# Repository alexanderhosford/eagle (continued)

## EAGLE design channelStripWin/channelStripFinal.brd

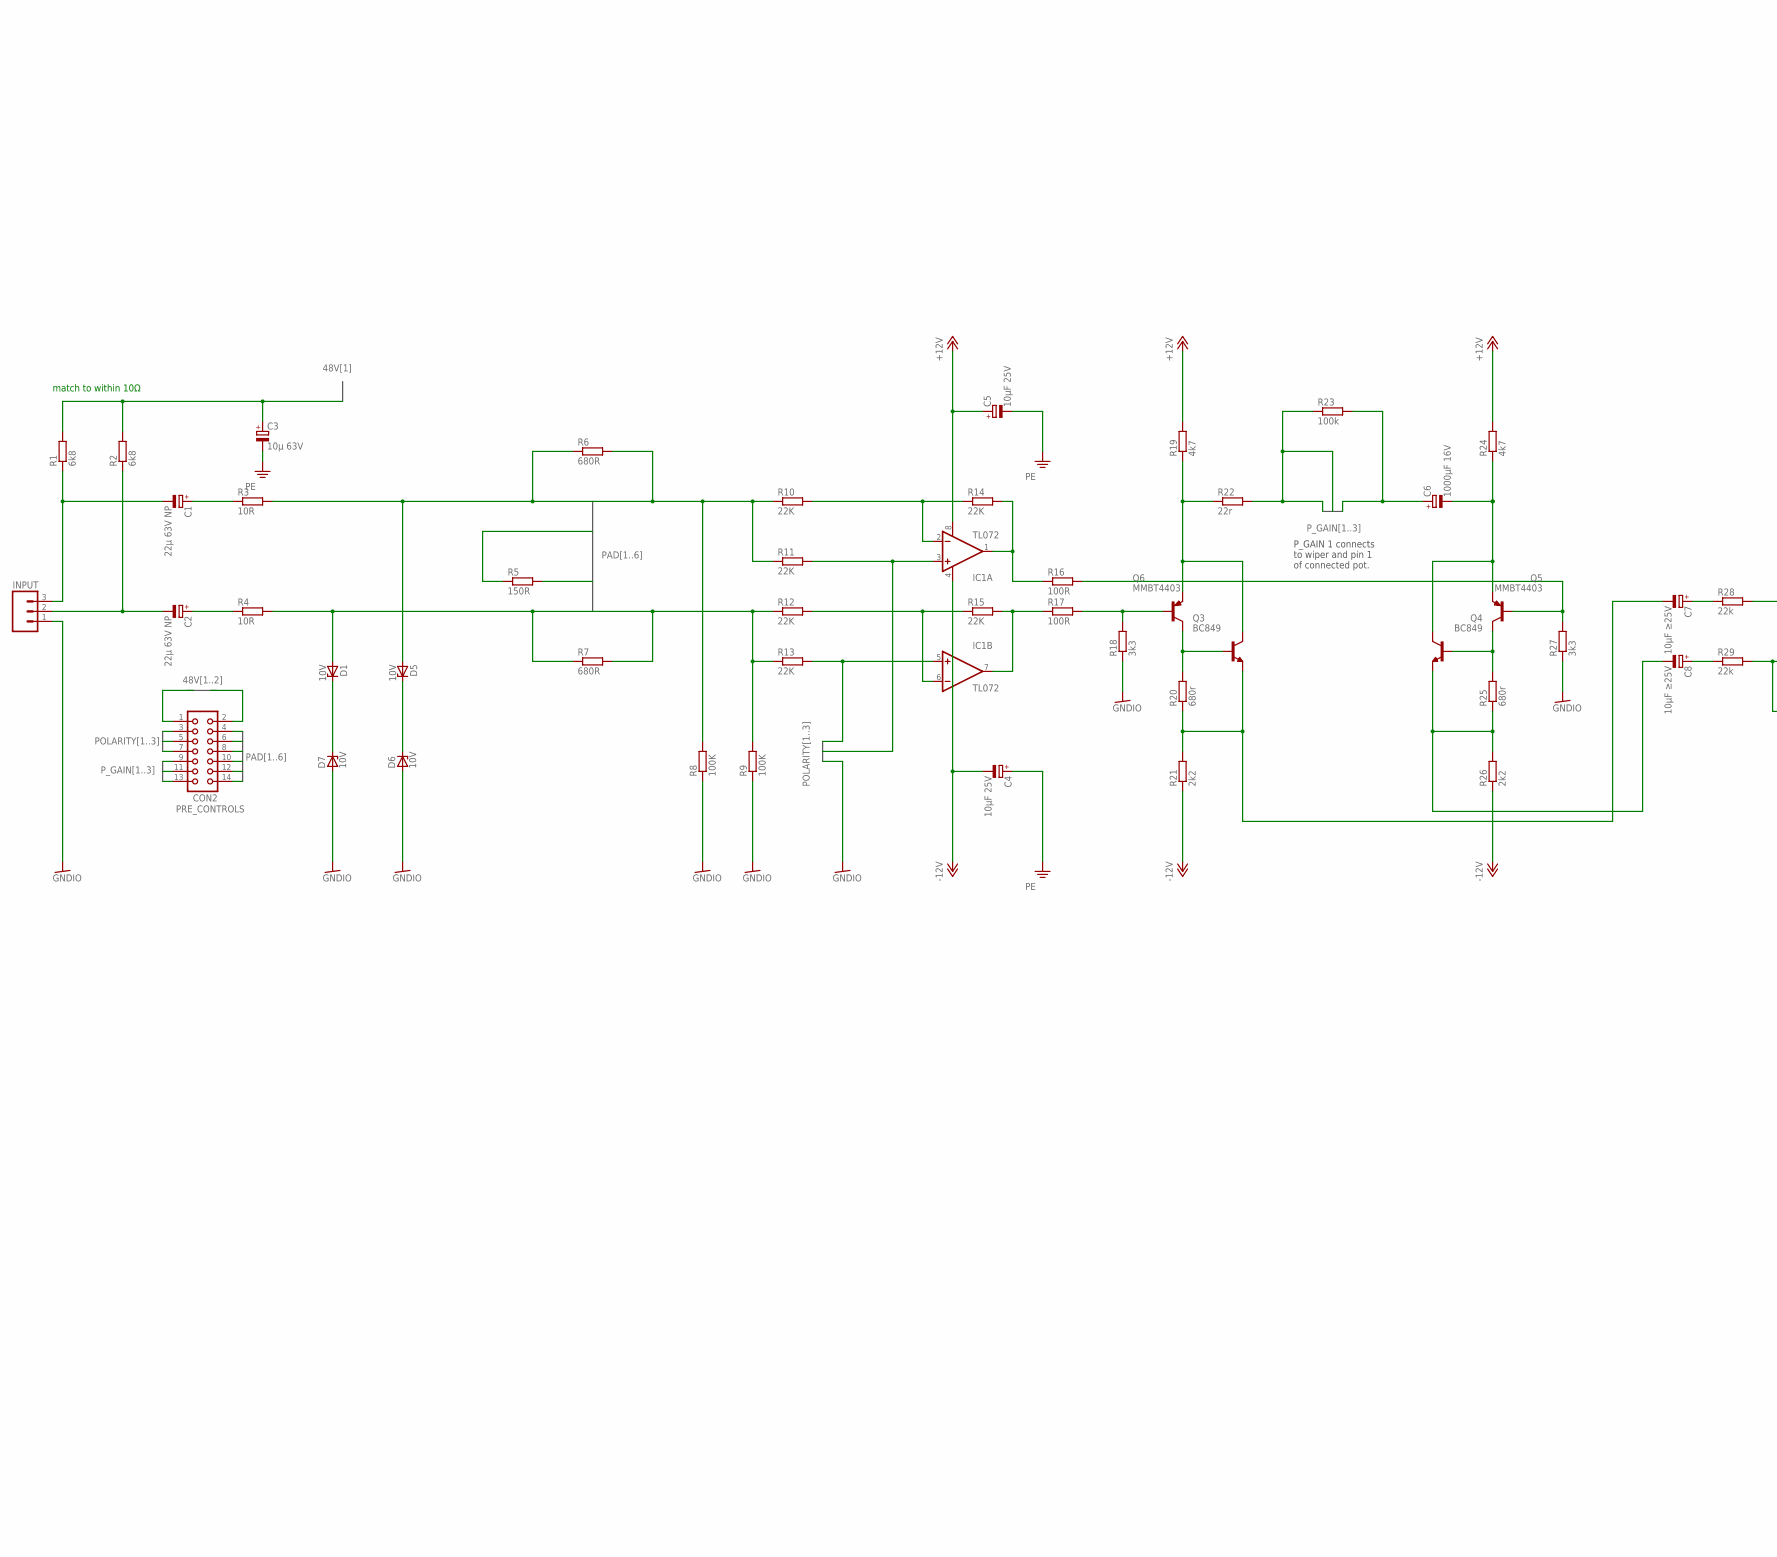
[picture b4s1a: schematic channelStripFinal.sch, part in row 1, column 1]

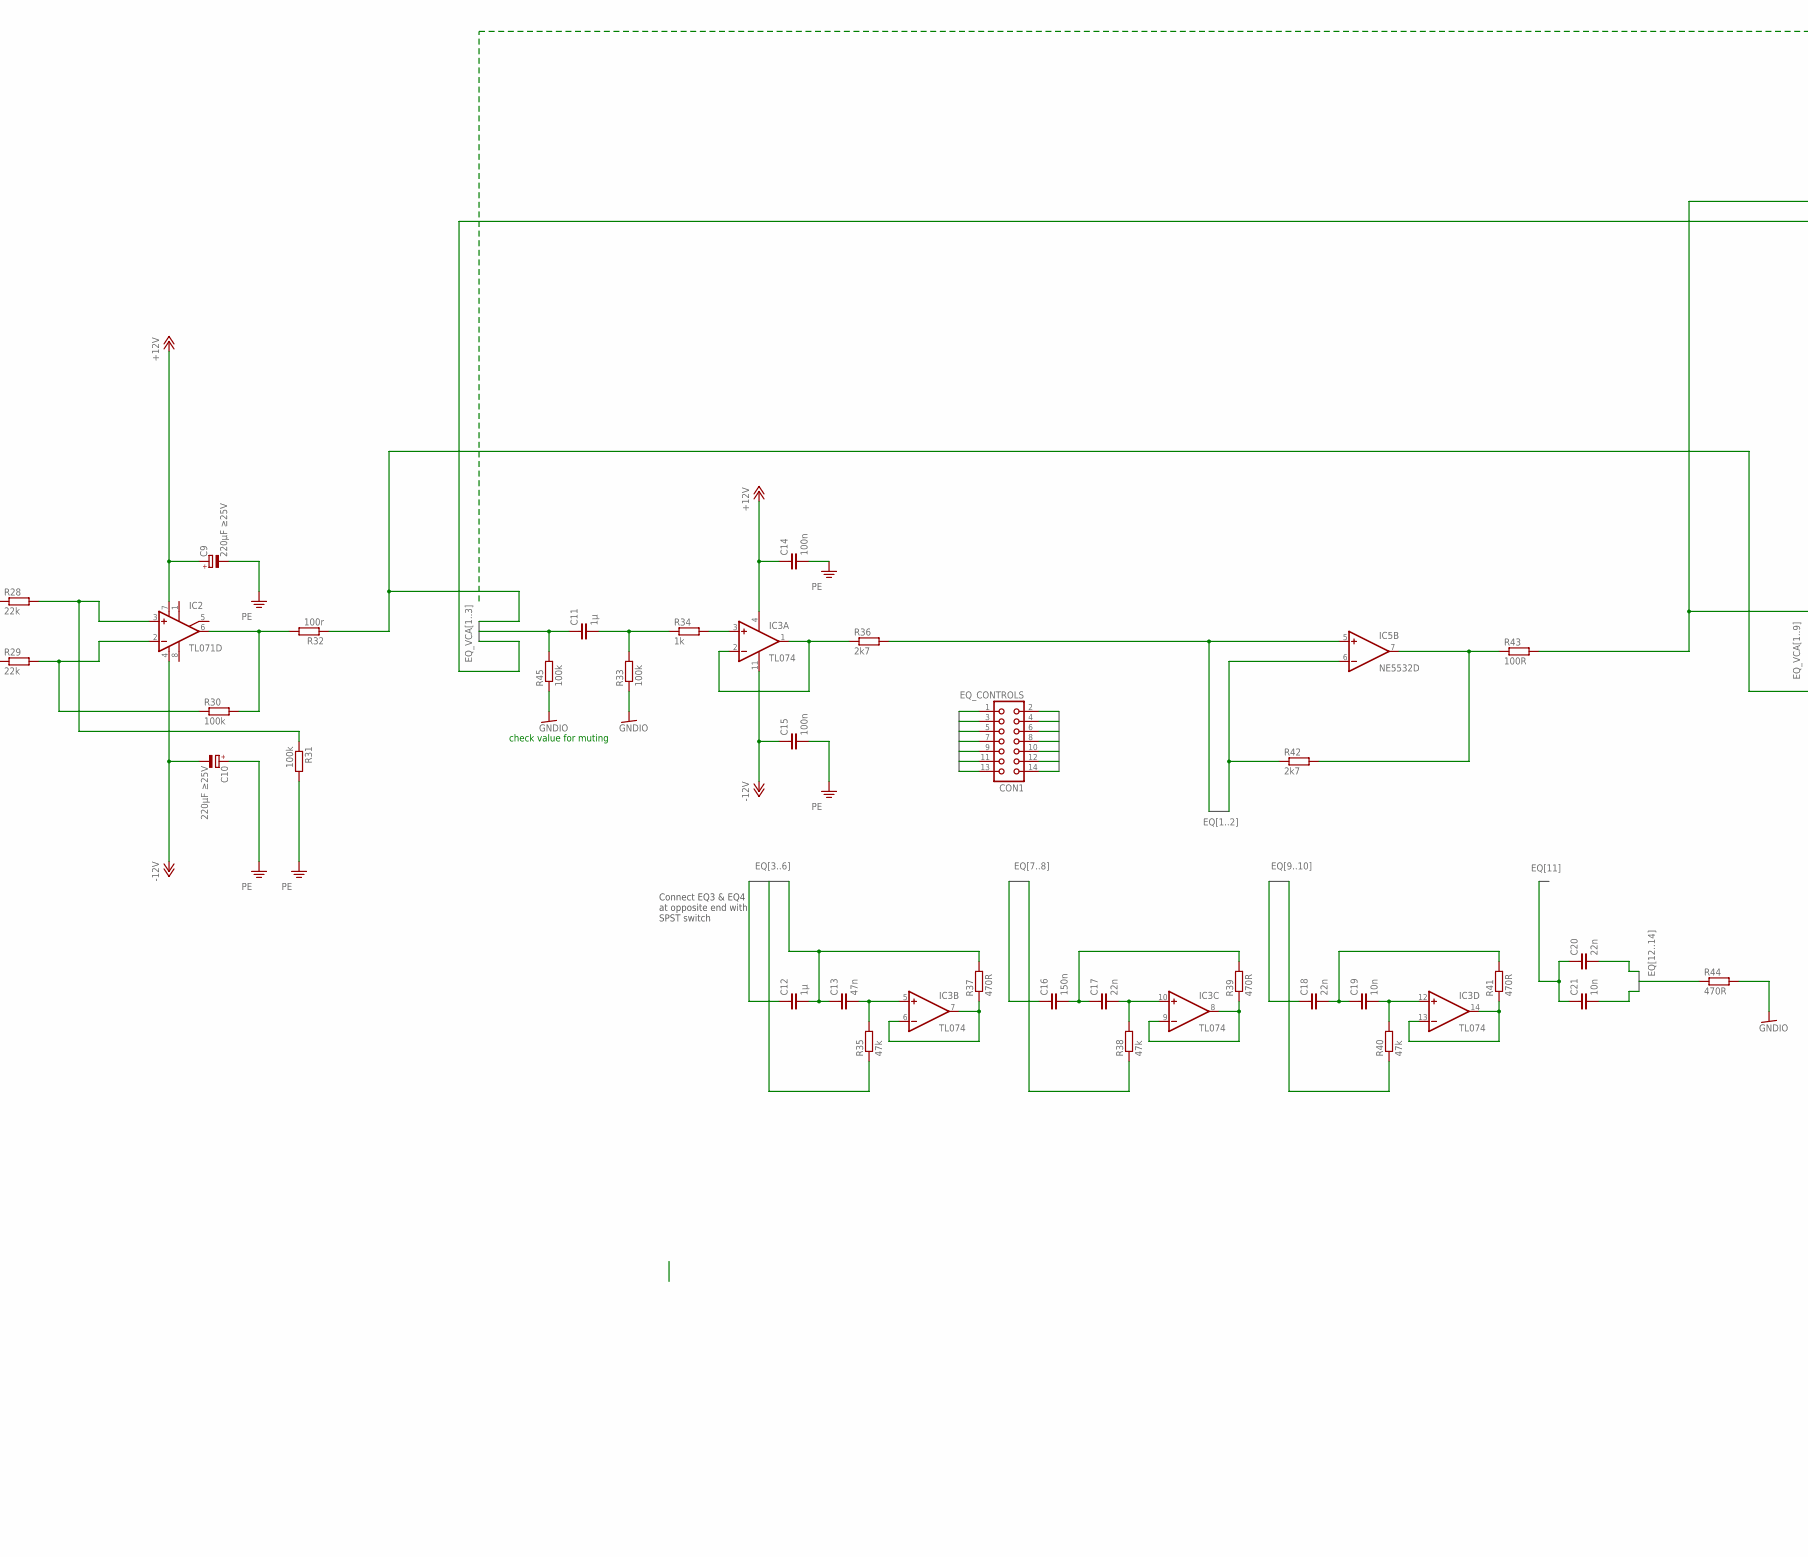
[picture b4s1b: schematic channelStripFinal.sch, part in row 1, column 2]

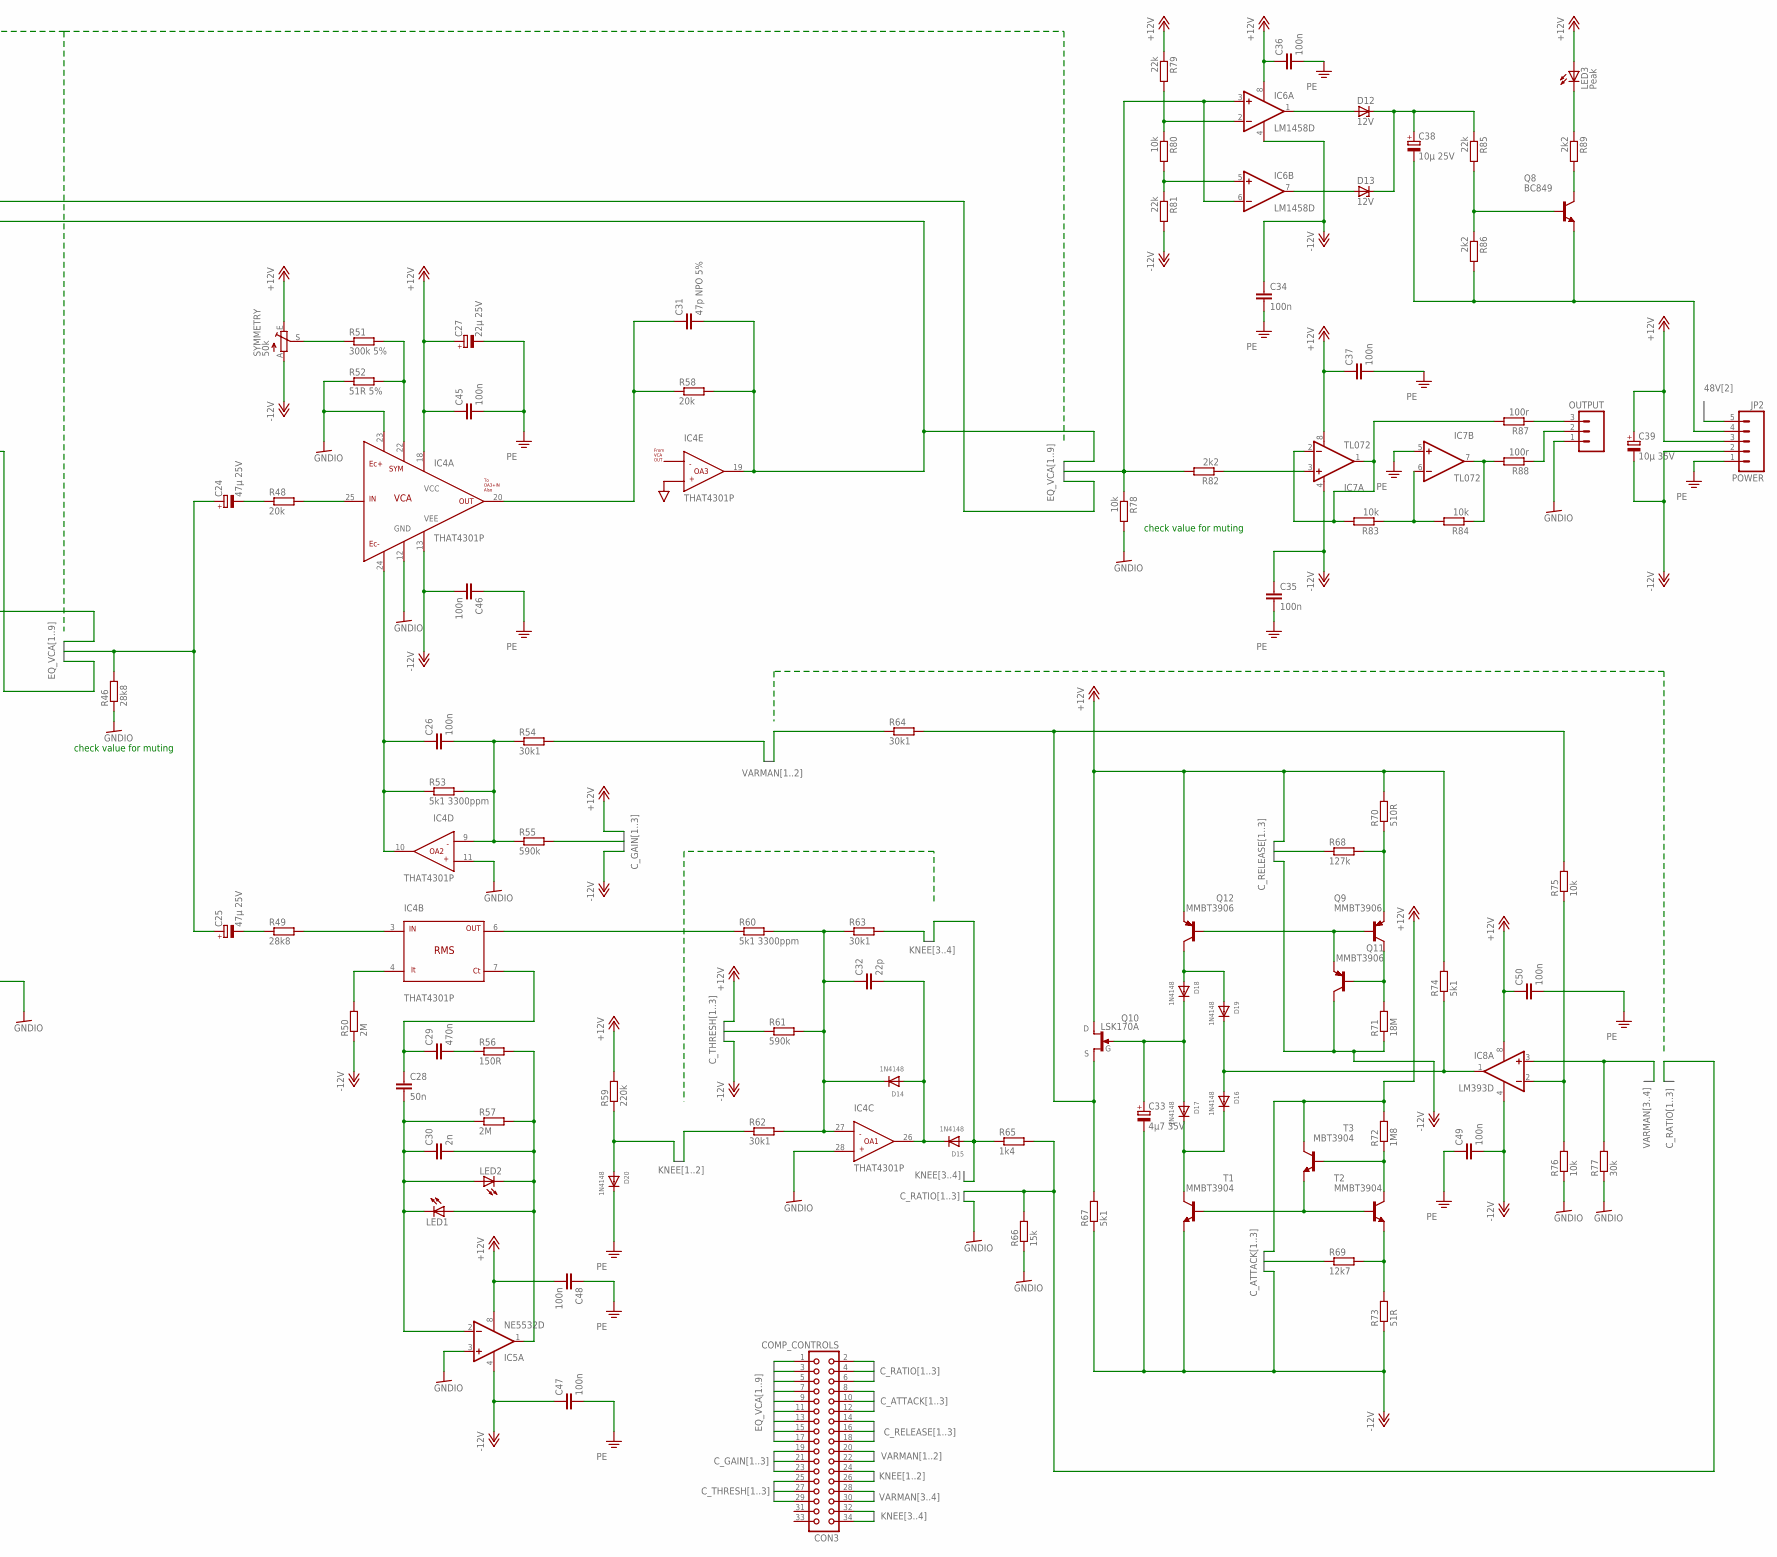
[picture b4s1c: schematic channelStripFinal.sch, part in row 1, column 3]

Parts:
C1, C2: 22µ 63V NP; E5-10,5
C3: 10µ 63V; E2-5
C4, C5: 10µF 25V; E1,8-4
C6: 1000µF 16V; E5-10,5
C7, C8: 10µF ≥25V; E1,8-4
C9, C10: 220µF ≥25V; E3,5-8
C11, C12: 1µ; C050-050X075
C13: 47n; C050-025X075
C14, C15, C26, C34, C35, C36, C37, C45, C46, C47, C48, C49, C50: 100n; C050-025X075
C16: 150n; C075-032X103
C17, C18, C20: 22n; C075-032X075
C19, C21: 10n; C050-025X075
C24, C25: 47µ 25V; E2,5-6
C27: 22µ 25V; E2-5
C28: 50n; C050-025X075
C29: 470n; C050-035X075
C30: 2n; C025-024X044
C31: 47p NPO 5%; C025-024X044
C32: 22p; C025-024X044
C33: 4µ7 35V; E2-4
C38: 10µ 25V; E1,8-4
C39: 10µ 35V; E1,8-4
CON1: EQ_CONTROLS; CON14
CON2: PRE_CONTROLS; CON14
CON3: COMP_CONTROLS; CON34
D1, D5, D6, D7: 10V; ZD-5-SMALLSILK
D12, D13: 12V; ZD-5-SMALLSILK
D14, D15, D16, D17, D18, D19, D20: 1N4148; SOD-123
IC1, IC7: TL072; SO08
IC2: TL071D; SO08
IC3: TL074; SO14
IC4: THAT4301P; SO30W
IC5: NE5532D; SO08
IC6: LM1458D; SO08
IC8: LM393D; SO08
INPUT: M03PTH; 1X03
JP2: POWER; 1X05
LED1, LED2: LED1206; LED-1206
LED3: Peak; LED-1206
OUTPUT: M03PTH; 1X03
Q3, Q4, Q8: BC849; SOT23
Q5, Q6: MMBT4403; SOT23-BEC
Q9, Q11, Q12: MMBT3906; SOT23-BEC
Q10: LSK170A; SOT23
R1, R2: 6k8; R1206
R3, R4: 10R; R1206
R5, R56: 150R; R1206
R6, R7: 680R; R1206
R8, R9: 100K; R1206
R10, R11, R12, R13, R14, R15: 22K; R1206
R16, R17, R43: 100R; R1206
R18, R27: 3k3; R1206
R19, R24: 4k7; R1206
R20, R25: 680r; R1206
R21, R26, R82, R86, R89: 2k2; R1206
R22: 22r; R1206
R23, R30, R31, R33, R45: 100k; R1206
R28, R29, R79, R81, R85: 22k; R1206
R32, R87, R88: 100r; R1206
R34: 1k; R1206
R35, R38, R40: 47k; R1206
R36, R42: 2k7; R1206
R37, R39, R41, R44: 470R; R1206
R46, R49: 28k8; R1206
R48, R58: 20k; R1206
R50, R57: 2M; R1206
R51: 300k 5%; R1206
R52: 51R 5%; R1206
R53, R60: 5k1 3300ppm; R1206
R54, R62, R63, R64: 30k1; R1206
R55, R61: 590k; R1206
R59: 220k; R1206
R65: 1k4; R1206
R66: 15k; R1206
R67, R74: 5k1; R1206
R68: 127k; R1206
R69: 12k7; R1206
R70: 510R; R1206
R71: 18M; R1206
R72: 1M8; R1206
R73: 51R; R1206
R75, R76, R78, R80, R83, R84: 10k; R1206
R77: 30k; R1206
SYMMETRY: 50k; B64W
T1, T2: MMBT3904; SOT23-BEC
T3: MBT3904; SOT23-BEC

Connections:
48V1: CON2.1
48V2: CON2.2, JP2.5
+12V: C5.+, C9.+, C14.1, C27.+, C36.1, C37.1, C39.+, C45.1, C48.2, C50.1, IC1.8 (V+), IC2.7 (V+), IC3.4 (V+), IC4.18 (VCC), IC5.8 (V+), IC6.8 (V+), IC7.8 (V+), IC8.8 (V+), JP2.3, LED3.A, R19.2, R24.2, R59.2, R79.1, SYMMETRY.E
-12V: C4.-, C10.-, C15.1, C34.1, C35.1, C39.-, C46.2, C47.1, C49.2, IC1.4 (V-), IC2.4 (V-), IC3.11 (V-), IC4.13 (VEE), IC5.4 (V-), IC6.4 (V-), IC7.4 (V-), IC8.4 (V-), JP2.2, R21.1, R26.1, R50.1, R81.2, SYMMETRY.A
C_ATTACK1: CON3.8, R72.2, T3.C
C_ATTACK2: CON3.10, R69.1
C_ATTACK3: C33.-, CON3.12, R67.1, R73.1, T1.E
C_GAIN1: CON3.19
C_GAIN2: CON3.21, R55.2
C_GAIN3: CON3.23
C_RATIO1: CON3.2
C_RATIO2: CON3.4, R65.2, R66.2
C_RATIO3: CON3.6
C_RELEASE1: CON3.14, Q10.1 (D), Q12.E, R70.2, R74.2
C_RELEASE2: CON3.16, R68.1
C_RELEASE3: CON3.18, Q11.C, R71.1
C_THRESH1: CON3.25
C_THRESH2: CON3.27, R61.1
C_THRESH3: CON3.29
EQ1: CON1.1, IC5.5 (+IN), R36.2
EQ2: CON1.2, IC5.6 (-IN), R42.1
EQ3: C12.1, CON1.3
EQ4: C12.2, C13.1, CON1.4, R37.2
EQ5: CON1.5, R35.1
EQ6: CON1.6
EQ7: C16.1, CON1.7
EQ8: CON1.8, R38.1
EQ9: C18.1, CON1.9
EQ10: CON1.10, R40.1
EQ11: C20.1, C21.1, CON1.11
EQ12: C20.2, CON1.12
EQ13: C21.2, CON1.13
EQ14: CON1.14, R44.1
EQ_VCA1: CON3.1, R32.1
EQ_VCA2: C11.1, CON3.3, R45.2
EQ_VCA3: C31.2, CON3.5, IC4.19 (OA3_OUT), R58.2
EQ_VCA4: CON3.7, R43.2
EQ_VCA5: C24.+, C25.+, CON3.9, R46.2
EQ_VCA6: CON3.11
EQ_VCA7: CON3.13
EQ_VCA8: CON3.15, IC6.3 (+IN), IC6.6 (-IN), R78.1, R82.2
EQ_VCA9: CON3.17
GNDIO: D6.A, D7.A, IC4.11 (OA2+IN), IC4.12 (GND), IC4.23 (EC+), IC4.28 (OA1+IN), IC5.3 (+IN), INPUT.1, OUTPUT.1, R8.1, R9.1, R18.1, R27.1, R33.1, R44.2, R45.1, R46.1, R52.1, R66.1, R76.1, R77.1, R78.2
KNEE1: CON3.24, D20.A, R59.1
KNEE2: CON3.26, R62.1
KNEE3: CON3.32, R63.2
KNEE4: CON3.34, D15.A, R65.1
unnamed: IC7.7 (OUT), R84.1, R88.2
unnamed: C7.-, Q3.2 (E), R20.1, R21.2
unnamed: C16.2, C17.1, R39.2
unnamed: C18.2, C19.1, R41.2
unnamed: IC3.13 (-IN), IC3.14 (OUT), R41.1
unnamed: C19.2, IC3.12 (+IN), R40.2
unnamed: C11.2, R33.2, R34.1
unnamed: IC3.3 (+IN), R34.2
unnamed: IC3.1 (OUT), IC3.2 (-IN), R36.1
unnamed: IC5.7 (OUT), R42.2, R43.1
unnamed: Q8.1 (B), R85.2, R86.1
unnamed: C1.+, R3.1
unnamed: IC3.6 (-IN), IC3.7 (OUT), R37.1
unnamed: C13.2, IC3.5 (+IN), R35.2
unnamed: IC3.8 (OUT), IC3.9 (-IN), R39.1
unnamed: C2.+, R4.1
unnamed: C17.2, IC3.10 (+IN), R38.2
unnamed: IC6.2 (-IN), R79.2, R80.1
unnamed: C1.-, INPUT.3, R1.1
unnamed: C2.-, INPUT.2, R2.1
unnamed: OUTPUT.2, R88.1
unnamed: OUTPUT.3, R87.1
unnamed: IC2.3 (+IN), R28.2, R31.1
unnamed: IC7.6 (-IN), R83.1, R84.2
unnamed: IC7.1 (OUT), IC7.2 (-IN), R83.2, R87.2
unnamed: IC7.3 (+IN), R82.1
unnamed: C7.+, R28.1
unnamed: IC2.6 (OUT), R30.2, R32.2
unnamed: IC2.2 (-IN), R29.2, R30.1
unnamed: C8.+, R29.1
unnamed: C6.-, Q4.3 (C), Q5.E, R24.1
unnamed: Q3.3 (C), Q6.E, R19.1, R22.1
unnamed: Q4.1 (B), Q5.C, R25.2
unnamed: IC1.1 (OUT), R14.2, R16.1
unnamed: Q3.1 (B), Q6.C, R20.2
unnamed: IC6.5 (+IN), R80.2, R81.1
unnamed: IC1.7 (OUT), R15.2, R17.1
unnamed: C8.-, Q4.2 (E), R25.1, R26.2
unnamed: Q5.B, R16.2, R27.2
unnamed: Q6.B, R17.2, R18.2
unnamed: IC1.6 (-IN), R12.2, R15.1
unnamed: D5.C, D6.C
unnamed: IC1.2 (-IN), R10.2, R14.1
unnamed: D1.C, D7.C
unnamed: Q8.3 (C), R89.2
unnamed: C38.+, D12.C, D13.C, R85.1
unnamed: LED3.C, R89.1
unnamed: D12.A, IC6.1 (OUT)
unnamed: D13.A, IC6.7 (OUT)
unnamed: IC4.25 (VCA_IN), R48.2
unnamed: C24.-, R48.1
unnamed: R51.1, SYMMETRY.S
unnamed: IC4.22 (SYM), R51.2, R52.2
unnamed: C31.1, IC4.20 (VCA_OUT), R58.1
unnamed: C26.1, IC4.10 (OA2_OUT), IC4.24 (EC-), R53.1
unnamed: C26.2, IC4.9 (OA2-IN), R53.2, R54.1, R55.1
unnamed: C29.2, R56.1
unnamed: C28.1, C29.1, IC4.7 (CT)
unnamed: C28.2, C30.1, IC5.2 (-IN), LED1.C, LED2.A, R57.1
unnamed: C30.2, IC5.1 (OUT), LED1.A, LED2.C, R56.2, R57.2
unnamed: IC4.4 (IT), R50.2
unnamed: IC4.3 (RMS_IN), R49.2
unnamed: C25.-, R49.1
unnamed: IC4.6 (RMS_OUT), R60.1
unnamed: C32.1, D14.C, IC4.27 (OA1-IN), R60.2, R61.2, R62.2, R63.1
unnamed: C32.2, D14.A, D15.C, IC4.26 (OA1_OUT)
unnamed: Q10.2 (S), R64.2, R67.2, R75.2
unnamed: C33.+, D17.A, D18.C, Q10.3 (G)
unnamed: D16.C, D17.C, T1.C
unnamed: D18.A, D19.A, Q12.C
unnamed: D16.A, D19.C, IC8.1 (OUT), R74.1
unnamed: T1.B, T2.B, T3.E
unnamed: R69.2, R73.2, T2.E
unnamed: R72.1, T2.C, T3.B
unnamed: Q9.B, Q11.E, Q12.B
unnamed: Q9.C, Q11.B, R71.2
unnamed: Q9.E, R68.2, R70.1
unnamed: IC8.2 (-IN), R75.1, R76.2
PAD1: CON2.4, R5.1
PAD2: CON2.6, R6.2, R8.2, R10.1, R11.1
PAD3: CON2.8, D5.A, R3.2, R6.1
PAD4: CON2.10, R5.2
PAD5: CON2.12, R7.2, R9.2, R12.1, R13.1
PAD6: CON2.14, D1.A, R4.2, R7.1
PE: C3.-, C4.+, C5.-, C9.-, C10.+, C14.2, C15.2, C27.-, C34.2, C35.2, C36.2, C37.2, C45.2, C46.1, C47.2, C48.1, C49.1, C50.2, D20.C, IC7.5 (+IN), JP2.1, R31.2
PEAKGND: C38.-, JP2.4, Q8.2 (E), R86.2
POLARITY1: CON2.3, IC1.5 (+IN), R13.2
POLARITY2: CON2.5, IC1.3 (+IN), R11.2
POLARITY3: CON2.7
PRE1: C3.+, R1.2, R2.2
P_GAIN1: CON2.9, R22.2, R23.1
P_GAIN2: CON2.11
P_GAIN3: C6.+, CON2.13, R23.2
VARMAN1: CON3.20, R54.2
VARMAN2: CON3.22, R64.1
VARMAN3: CON3.28, IC8.3 (+IN), R77.2
VARMAN4: CON3.30

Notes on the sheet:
match to within 10Ω
check value for muting
Connect EQ3 & EQ4 at opposite end with SPST switch
P_GAIN 1 connects to wiper and pin 1 of connected pot.

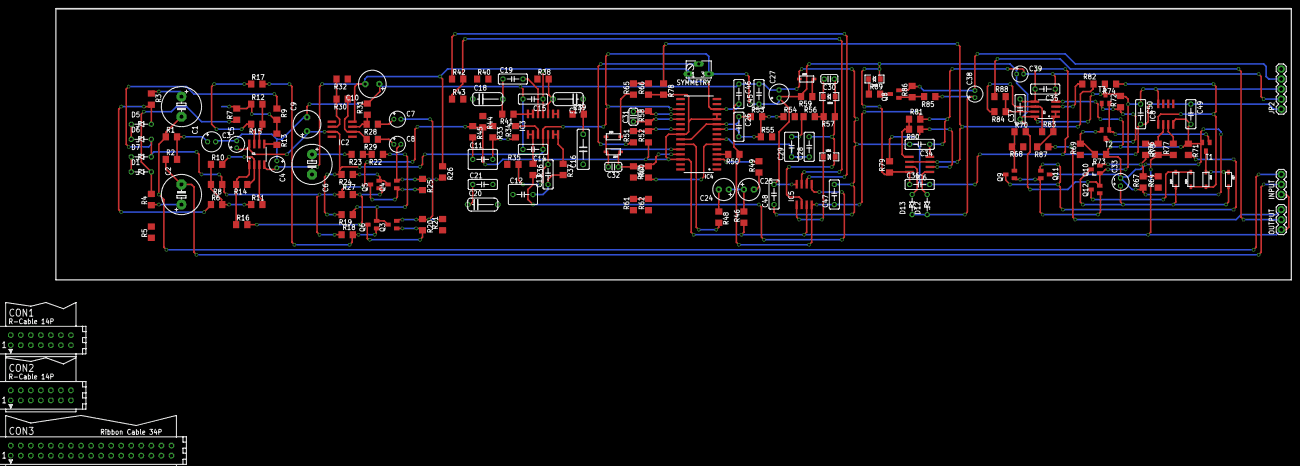
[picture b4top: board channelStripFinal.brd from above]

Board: 2 copper layers, 312.4 x 68.6 mm, 174 parts (0 on the bottom side), 130 nets.

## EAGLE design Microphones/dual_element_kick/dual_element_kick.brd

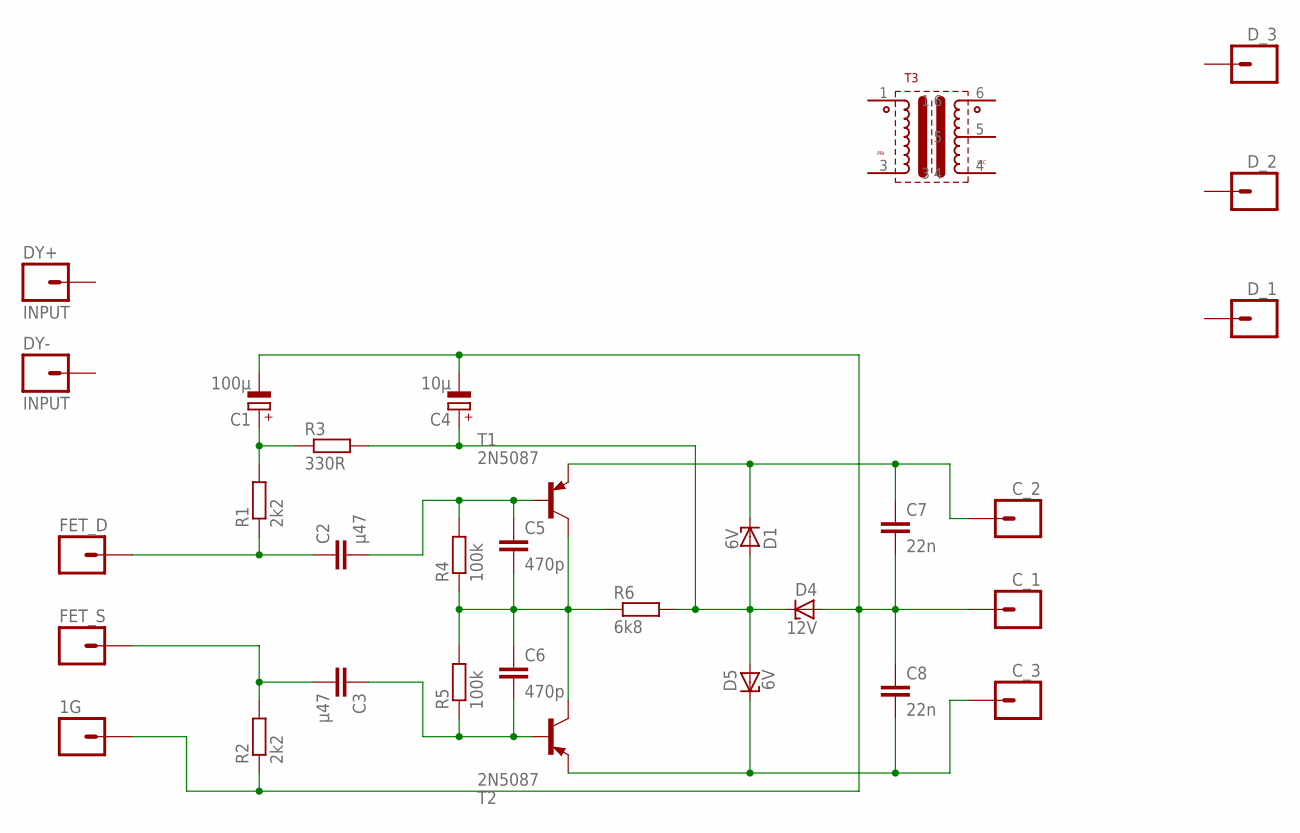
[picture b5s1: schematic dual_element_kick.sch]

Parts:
1G: M01PTH; 1X01
C1: 100µ; E3,5-8
C2, C3: µ47; C050-045X075
C4: 10µ; E2-4
C5, C6: 470p; C025-024X044
C7, C8: 22n; C025-024X044
C_1, C_2, C_3: M01PTH; 1X01
D1, D5: 6V; ZD-5-SMALLSILK
D4: 12V; ZD-5-SMALLSILK
DY+: INPUT; 1X01
DY-: INPUT; 1X01
D_1, D_2, D_3: M01PTH; 1X01
FET_D: M01PTH; 1X01
FET_S: M01PTH; 1X01
R1, R2: 2k2; 0207/2V
R3: 330R; 0207/2V
R4, R5: 100k; 0207/2V
R6: 6k8; 0207/2V
T1, T2: 2N5087; TO92-EBC
T3: OEP-Z1604

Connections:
5: T3.5
GND: 1G.1, C1.-, C4.-, C7.2, C8.1, C_1.1, D4.A, R2.1
unnamed: C4.+, D1.A, D4.C, D5.A, R3.2, R6.2
unnamed: C5.2, C6.1, R4.1, R5.2, R6.1, T1.C, T2.C
unnamed: C7.1, C_2.1, D1.C, T1.E
unnamed: C8.2, C_3.1, D5.C, T2.E
unnamed: C2.2, C5.1, R4.2, T1.B
unnamed: C3.1, C6.2, R5.1, T2.B
unnamed: C1.+, R1.2, R3.1
unnamed: C2.1, FET_D.1, R1.1
unnamed: C3.2, FET_S.1, R2.2

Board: 2 copper layers, 31 parts (0 on the bottom side), 10 nets, no tracks yet.

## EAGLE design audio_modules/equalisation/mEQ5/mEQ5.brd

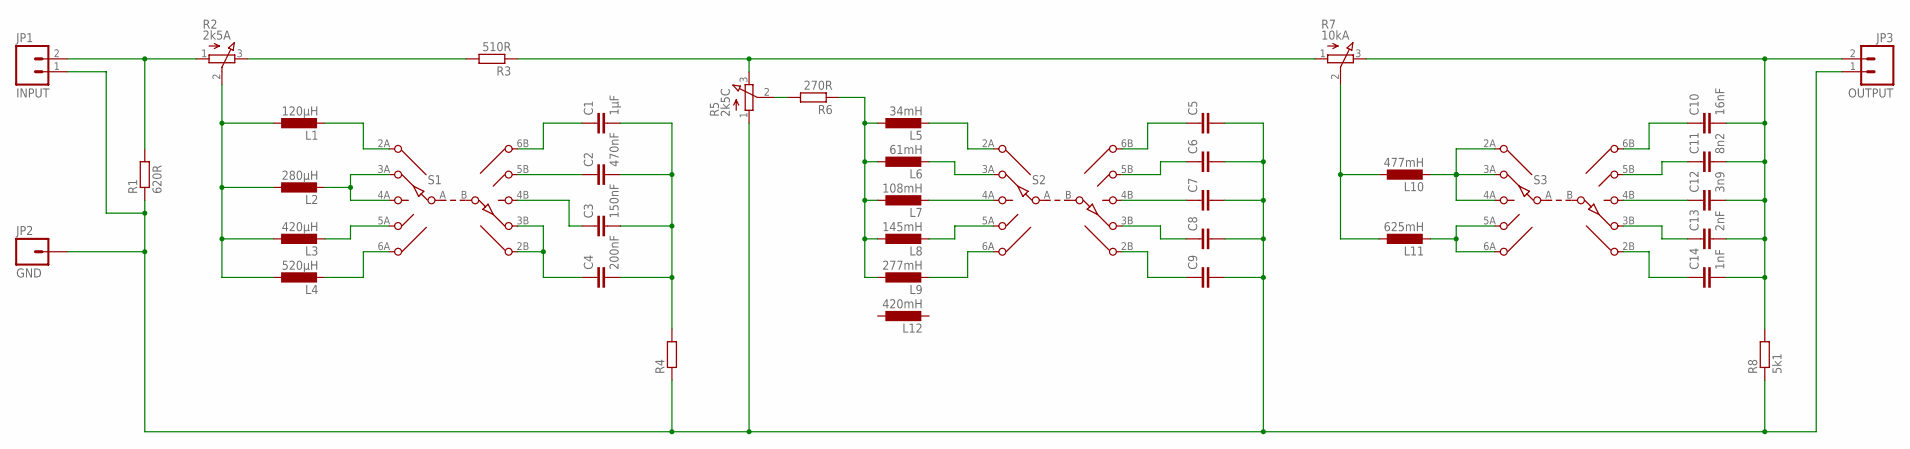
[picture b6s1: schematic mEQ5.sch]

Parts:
C1: 1µF; C050-025X075
C2: 470nF; C050-025X075
C3: 150nF; C050-025X075
C4: 200nF; C050-025X075
C5, C6, C7, C8, C9: C-EU050-025X075; C050-025X075
C10: 16nF; C050-025X075
C11: 8n2; C050-025X075
C12: 3n9; C050-025X075
C13: 2nF; C050-025X075
C14: 1nF; C050-025X075
JP1: INPUT; SCREWTERMINAL-3.5MM-2
JP2: GND; 1X01_LONGPAD
JP3: OUTPUT; SCREWTERMINAL-3.5MM-2
L1: 120µH; 0207/10
L2: 280µH; 0207/10
L3: 420µH; 0207/10
L4: 520µH; 0207/10
L5: 34mH; 0207/10
L6: 61mH; 0207/10
L7: 108mH; 0207/10
L8: 145mH; 0207/10
L9: 277mH; 0207/10
L10: 477mH; 0207/10
L11: 625mH; 0207/10
L12: 420mH; 0207/10
R1: 620R; 0207/10
R2: 2k5A; 3RP/1610N
R3: 510R; 0207/10
R4: R-EU_0207/10; 0207/10
R5: 2k5C; 3RP/1610N
R6: 270R; 0207/10
R7: 10kA; 3RP/1610N
R8: 5k1; 0207/10
S1, S2, S3: 5-POS-DP-ROTARY-SWITCH; 5-POS-DP-ROTARY

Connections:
unnamed: C3.1, S1.4B (2)
unnamed: L10.2, S3.2A (7), S3.3A (3), S3.4A (5)
unnamed: L1.2, S1.2A (7)
unnamed: L2.2, S1.3A (3), S1.4A (5)
unnamed: L11.2, S3.5A (6), S3.6A (9)
unnamed: C10.1, S3.6B (10)
unnamed: L3.2, S1.5A (6)
unnamed: L4.2, S1.6A (9)
unnamed: C1.1, S1.6B (10)
unnamed: C2.1, S1.5B (4)
unnamed: C4.1, S1.2B (8), S1.3B (1)
unnamed: C11.1, S3.5B (4)
unnamed: C12.1, S3.4B (2)
unnamed: C13.1, S3.3B (1)
unnamed: C14.1, S3.2B (8)
unnamed: L5.2, S2.2A (7)
unnamed: L6.2, S2.3A (3)
unnamed: L7.2, S2.4A (5)
unnamed: L8.2, S2.5A (6)
unnamed: L9.2, S2.6A (9)
unnamed: C5.1, S2.6B (10)
unnamed: C6.1, S2.5B (4)
unnamed: C7.1, S2.4B (2)
unnamed: C8.1, S2.3B (1)
unnamed: C9.1, S2.2B (8)
unnamed: L1.1, L2.1, L3.1, L4.1, R2.2 (S)
unnamed: JP1.2, R1.2, R2.1 (A)
unnamed: C1.2, C2.2, C3.2, C4.2, R4.2
unnamed: R2.3 (E), R3.2
unnamed: R3.1, R5.3 (E), R7.1 (A)
unnamed: R5.2 (S), R6.2
unnamed: L5.1, L6.1, L7.1, L8.1, L9.1, R6.1
unnamed: L10.1, L11.1, R7.2 (S)
unnamed: C5.2, C6.2, C7.2, C8.2, C9.2, JP1.1, JP2.1, JP3.1, R1.1, R4.1, R5.1 (A), R8.1
unnamed: C10.2, C11.2, C12.2, C13.2, C14.2, JP3.2, R7.3 (E), R8.2

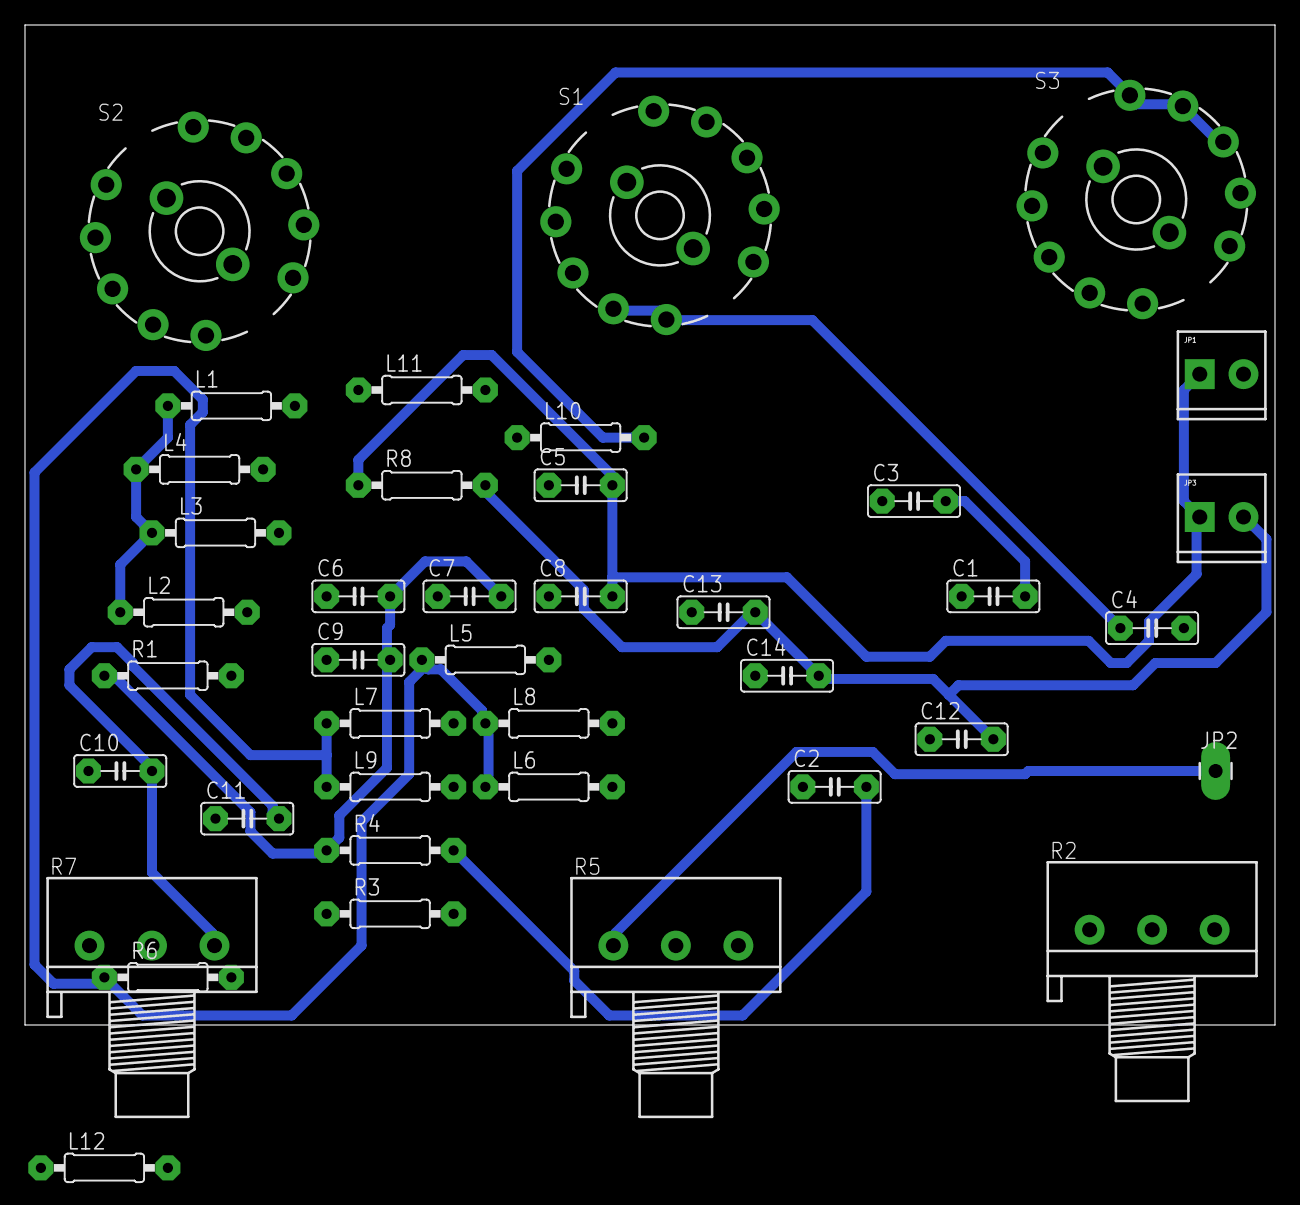
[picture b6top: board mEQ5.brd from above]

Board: 2 copper layers, 100.0 x 80.0 mm, 40 parts (0 on the bottom side), 35 nets.

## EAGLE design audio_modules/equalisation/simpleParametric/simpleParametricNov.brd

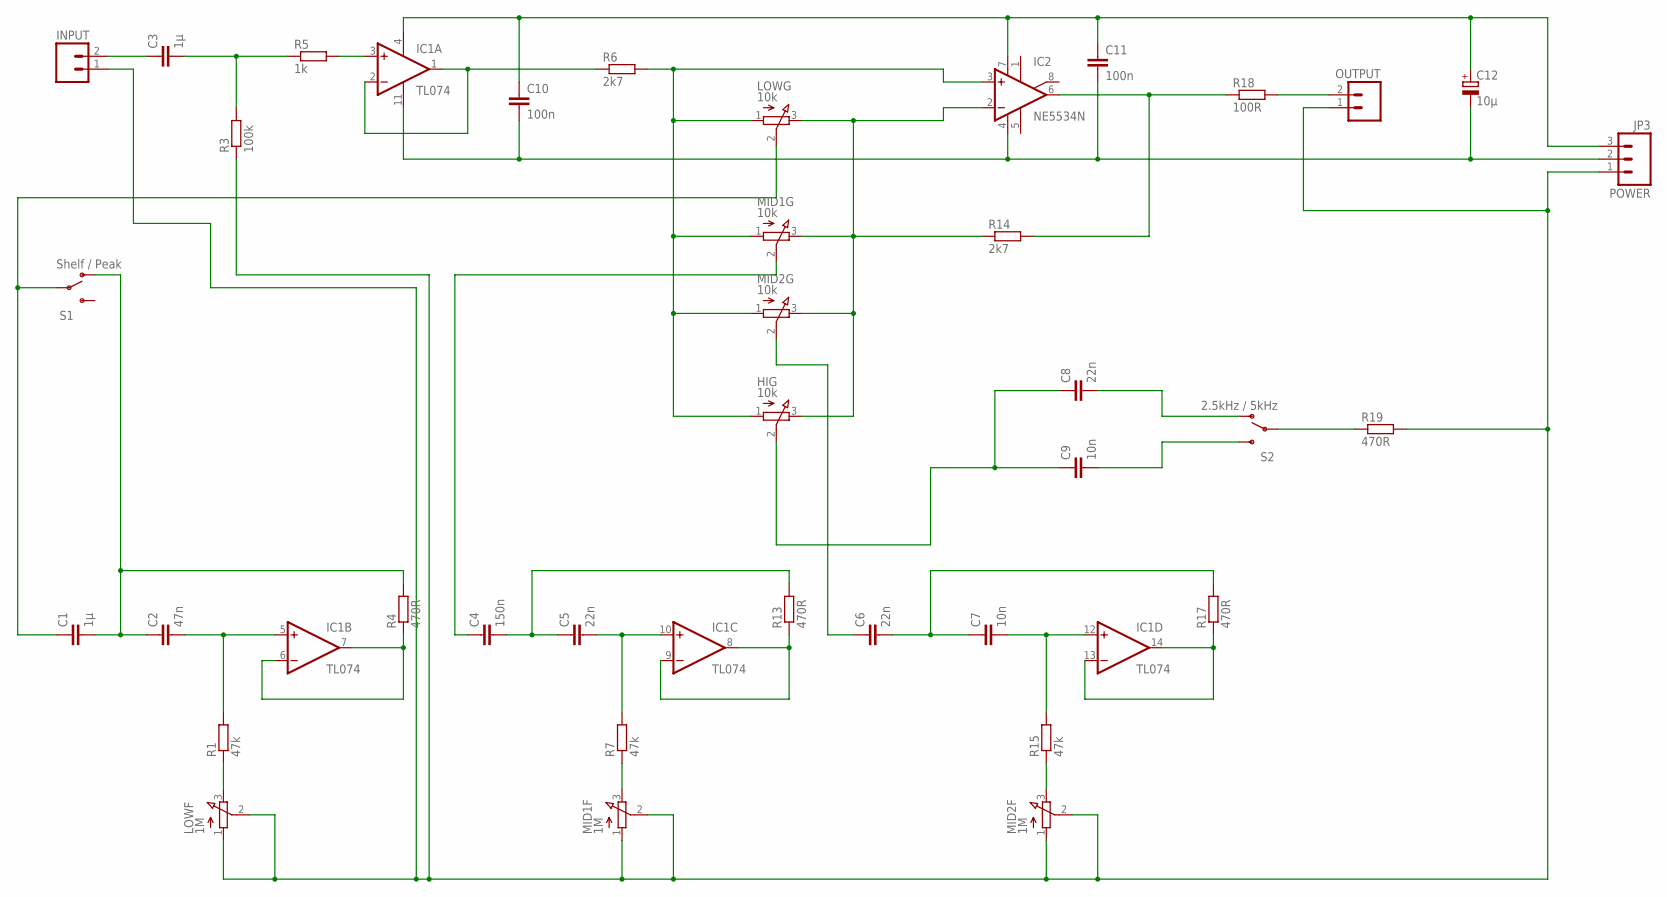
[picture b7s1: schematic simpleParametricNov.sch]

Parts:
C1, C3: 1µ; C050-025X075
C2: 47n; C050-025X075
C4: 150n; C050-025X075
C5, C6, C8: 22n; C025-024X044
C7, C9: 10n; C025-024X044
C10, C11: 100n; C050-025X075
C12: 10µ; E2,5-6E
HIG: 10k; 3RP/1610N
IC1: TL074; DIL14
IC2: NE5534N; DIL08
INPUT: M02PTH; 1X02
JP3: POWER; SCREWTERMINAL-3.5MM-3
LOWF: 1M; 3RP/1610N
LOWG: 10k; 3RP/1610N
MID1F, MID2F: 1M; 3RP/1610N
MID1G, MID2G: 10k; 3RP/1610N
OUTPUT: M02PTH; 1X02
R1, R7, R15: 47k; 0207/7
R3: 100k; 0207/7
R4, R13, R17, R19: 470R; 0207/7
R5: 1k; 0207/7
R6, R14: 2k7; 0207/7
R18: 100R; 0207/7
S1: Shelf / Peak; SWITCH-SPDT
S2: 2.5kHz / 5kHz; SWITCH-SPDT

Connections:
GND: INPUT.1, JP3.1, LOWF.1 (A), LOWF.2 (S), MID1F.1 (A), MID1F.2 (S), MID2F.1 (A), MID2F.2 (S), OUTPUT.1, R3.1, R19.2
unnamed: C1.2, C2.1, R4.2, S1.1 (O)
unnamed: C4.2, C5.1, R13.2
unnamed: C6.2, C7.1, R17.2
unnamed: C9.2, S2.3 (S)
unnamed: C8.2, S2.1 (O)
unnamed: R19.1, S2.2
unnamed: IC1.13 (-IN), IC1.14 (OUT), R17.1
unnamed: C7.2, IC1.12 (+IN), R15.2
unnamed: MID2F.3 (E), R15.1
unnamed: C3.1, INPUT.2
unnamed: C3.2, R3.2, R5.1
unnamed: IC1.3 (+IN), R5.2
unnamed: IC1.1 (OUT), IC1.2 (-IN), R6.1
unnamed: HIG.1 (A), IC2.3 (+IN), LOWG.1 (A), MID1G.1 (A), MID2G.1 (A), R6.2
unnamed: IC2.6 (OUT), R14.2, R18.1
unnamed: OUTPUT.2, R18.2
unnamed: HIG.3 (E), IC2.2 (-IN), LOWG.3 (E), MID1G.3 (E), MID2G.3 (E), R14.1
unnamed: IC1.6 (-IN), IC1.7 (OUT), R4.1
unnamed: C2.2, IC1.5 (+IN), R1.2
unnamed: LOWF.3 (E), R1.1
unnamed: C1.1, LOWG.2 (S), S1.2
unnamed: IC1.8 (OUT), IC1.9 (-IN), R13.1
unnamed: C5.2, IC1.10 (+IN), R7.2
unnamed: MID1F.3 (E), R7.1
unnamed: C6.1, MID2G.2 (S)
unnamed: C8.1, C9.1, HIG.2 (S)
V+: C10.1, C11.1, C12.+, IC1.4 (V+), IC2.7 (V+), JP3.3
V-: C10.2, C11.2, C12.-, IC1.11 (V-), IC2.4 (V-), JP3.2
VIA1: C4.1, MID1G.2 (S)

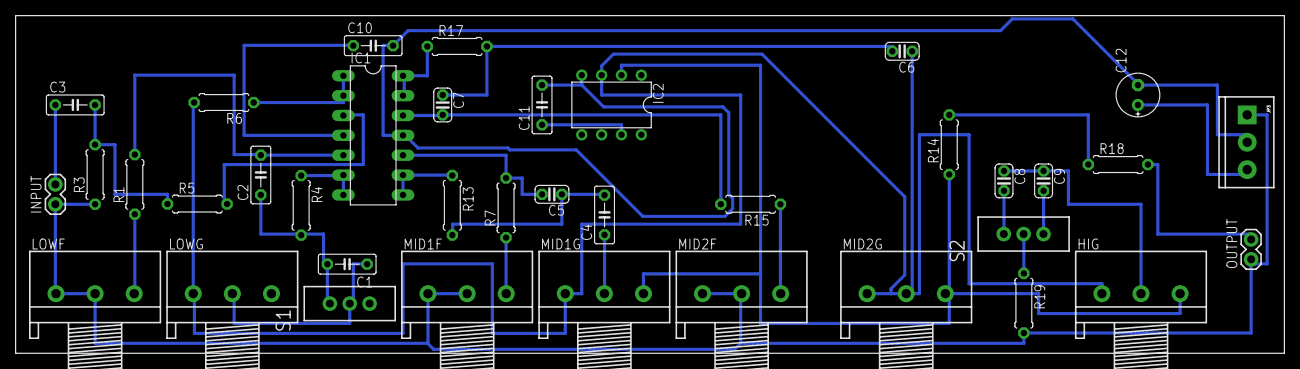
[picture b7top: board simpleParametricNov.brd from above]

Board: 2 copper layers, 162.2 x 43.2 mm, 38 parts (0 on the bottom side), 30 nets.

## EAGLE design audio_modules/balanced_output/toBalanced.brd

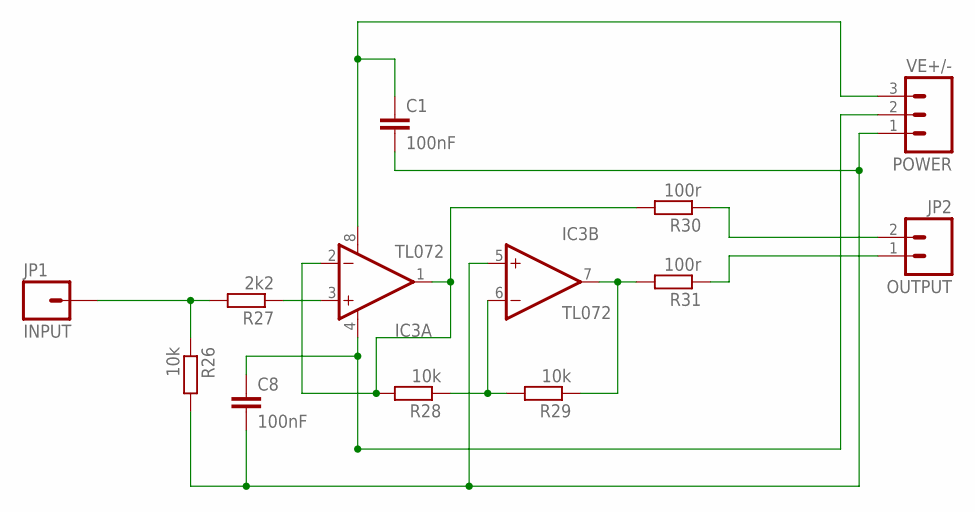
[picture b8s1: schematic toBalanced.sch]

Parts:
C1, C8: 100nF; C050-025X075
IC3: TL072; DIP08
JP1: INPUT; 1X01
JP2: OUTPUT; SCREWTERMINAL-3.5MM-2
R26, R28, R29: 10k; 0207/7
R27: 2k2; 0207/7
R30, R31: 100r; 0207/7
VE+/-: POWER; SCREWTERMINAL-3.5MM-3

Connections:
15V+: C1.1, IC3.8 (V+), VE+/-.3
15V-: C8.1, IC3.4 (V-), VE+/-.2
GND: C1.2, C8.2, IC3.5 (+IN), R26.2, VE+/-.1
unnamed: JP1.1, R26.1, R27.2
unnamed: IC3.7 (OUT), R29.1, R31.2
unnamed: JP2.1, R31.1
unnamed: JP2.2, R30.1
unnamed: IC3.6 (-IN), R28.1, R29.2
unnamed: IC3.1 (OUT), IC3.2 (-IN), R28.2, R30.2
unnamed: IC3.3 (+IN), R27.1
